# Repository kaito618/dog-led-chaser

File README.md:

# dog-led-chaser
a led chaser shaped as a dog
i am making a ledchaser that looks like a dog 
i started with the schematic connected everything 

and then i started with the pcb and at the time i haven't chose what shape my pcb will be so i started messing around with the parts and checking best places to put them in 
then i got the idea of making it a dog and started with the first reference 

and thta's how it ended up looking like 

[https://public.lapse-hackclub.link/timelapses/_K7J_XBW36Uw/thumbnail-_K7J_XBW36Uw.avif
](https://lapse.hackclub.com/timelapse/_K7J_XBW36Uw)

i didn't like how it looked like so i changed to this reference 

and that's how it looked like 

and as u see i alr connected everything 

https://lapse.hackclub.com/timelapse/kxh_GcCyjDND

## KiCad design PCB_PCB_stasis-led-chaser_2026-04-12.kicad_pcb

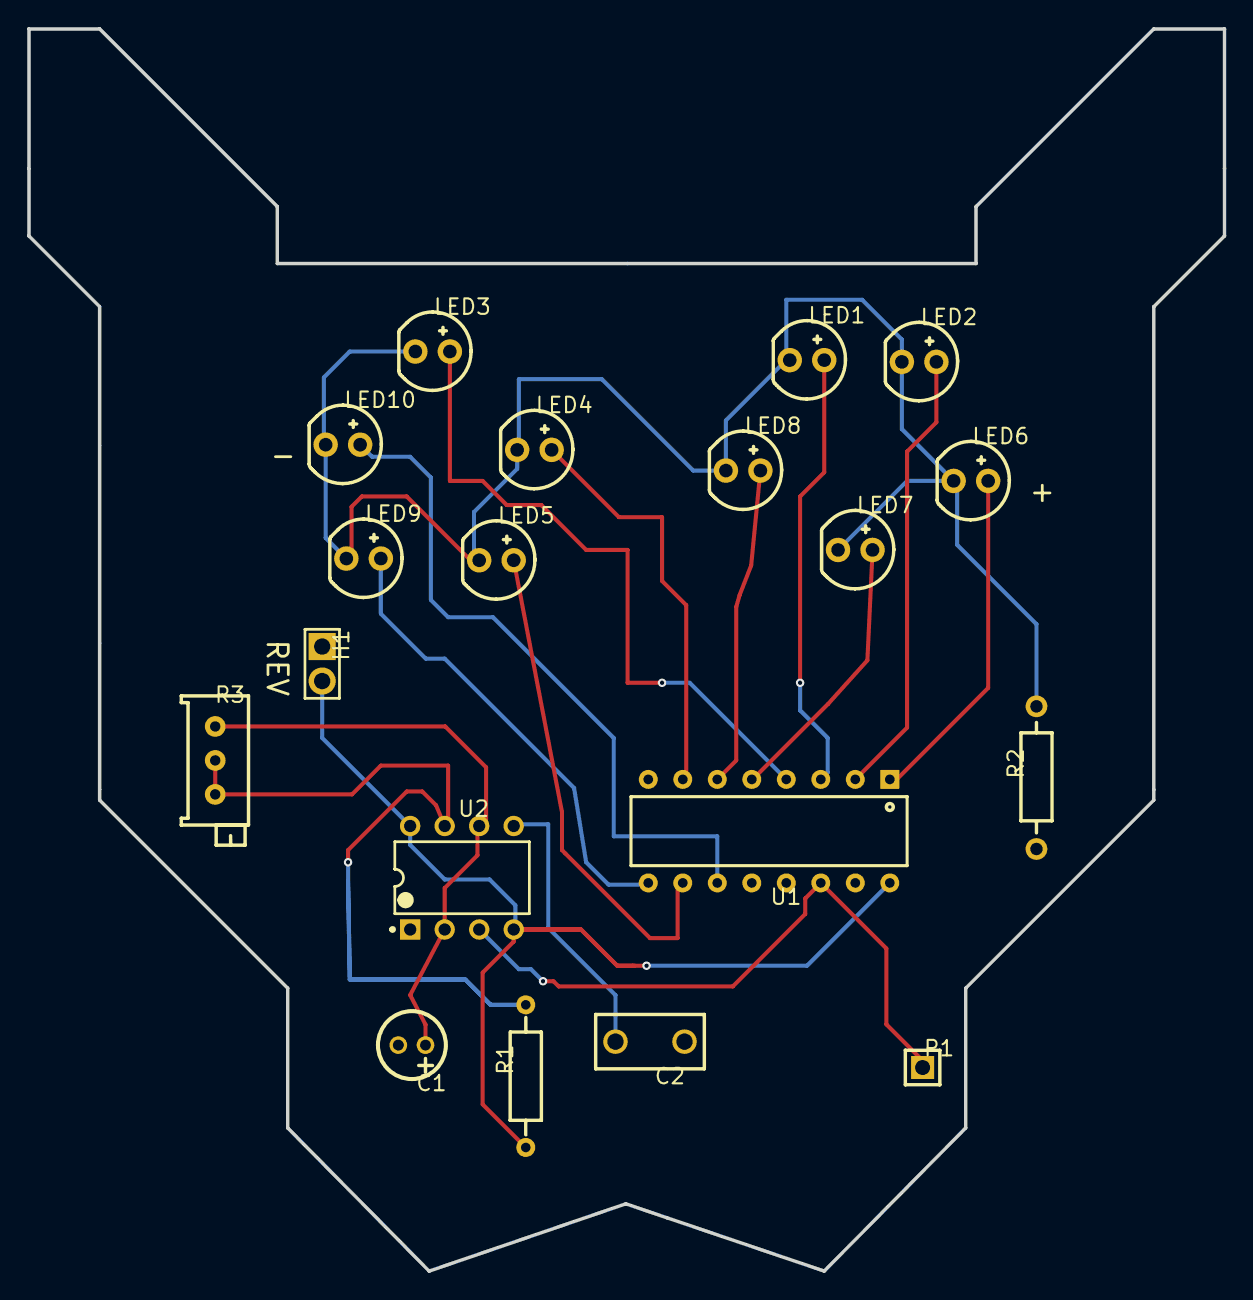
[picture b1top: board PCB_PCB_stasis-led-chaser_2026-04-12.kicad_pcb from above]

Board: 2 copper layers, 88.0 x 91.4 mm, 19 parts (0 on the bottom side), 17 nets.

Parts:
C1: 1uF; CAP-TH_BD5.0-P2.00-D0.8-FD
C2: 10nF; CAP-TH_L8.0-W4.0-P5.00-D1.2
H1: PZ254V-11-02P; HDR-TH_2P-P2.54-V-M
LED1, LED2, LED3, LED4, LED5, LED6, LED7, LED8, LED9, LED10: .; LED-TH_BD5.9-P2.54-RD_WHITE
P1: clk; HDR-TH_1P-P2.54-V-M
R1: 1kΩ; RES-TH_BD2.3-L6.5-P10.50-D0.5
R2: 470Ω; RES-TH_BD2.2-L6.5-P10.50-D0.6
R3: 50kΩ; RES-ADJ-TH_3P-L9.5-W4.85-P2.50-BL-L
U1: CD4017BCN; DIP16
U2: 100kHz; DIP-8_L9.8-W6.6-P2.54-LS7.6-BL

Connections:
1: LED1.2, U1.3
2: LED2.2, U1.2
3: LED3.2, U1.4
4: LED4.2, U1.7
5: LED5.2, U1.10
6: LED6.2, U1.1
7: LED7.2, U1.5
8: LED8.2, U1.6
9: LED9.2, U1.9
10: LED10.2, U1.11
C2_2: C2.2, U2.5
LED10_1: LED1.1, LED2.1, LED3.1, LED4.1, LED5.1, LED6.1, LED7.1, LED8.1, LED9.1, LED10.1, R2.2
P1_1: P1.1, U1.14, U2.3
R1_1: H1.2, R1.1, U1.16, U2.4, U2.8
R2_1: C1.2, C2.1, H1.1, R2.1, U1.8, U1.13, U1.15, U2.1
R3_1: C1.1, R3.1, U2.2, U2.6
R3_2: R1.2, R3.2, R3.3, U2.7

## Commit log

2026-04-05 Create s
